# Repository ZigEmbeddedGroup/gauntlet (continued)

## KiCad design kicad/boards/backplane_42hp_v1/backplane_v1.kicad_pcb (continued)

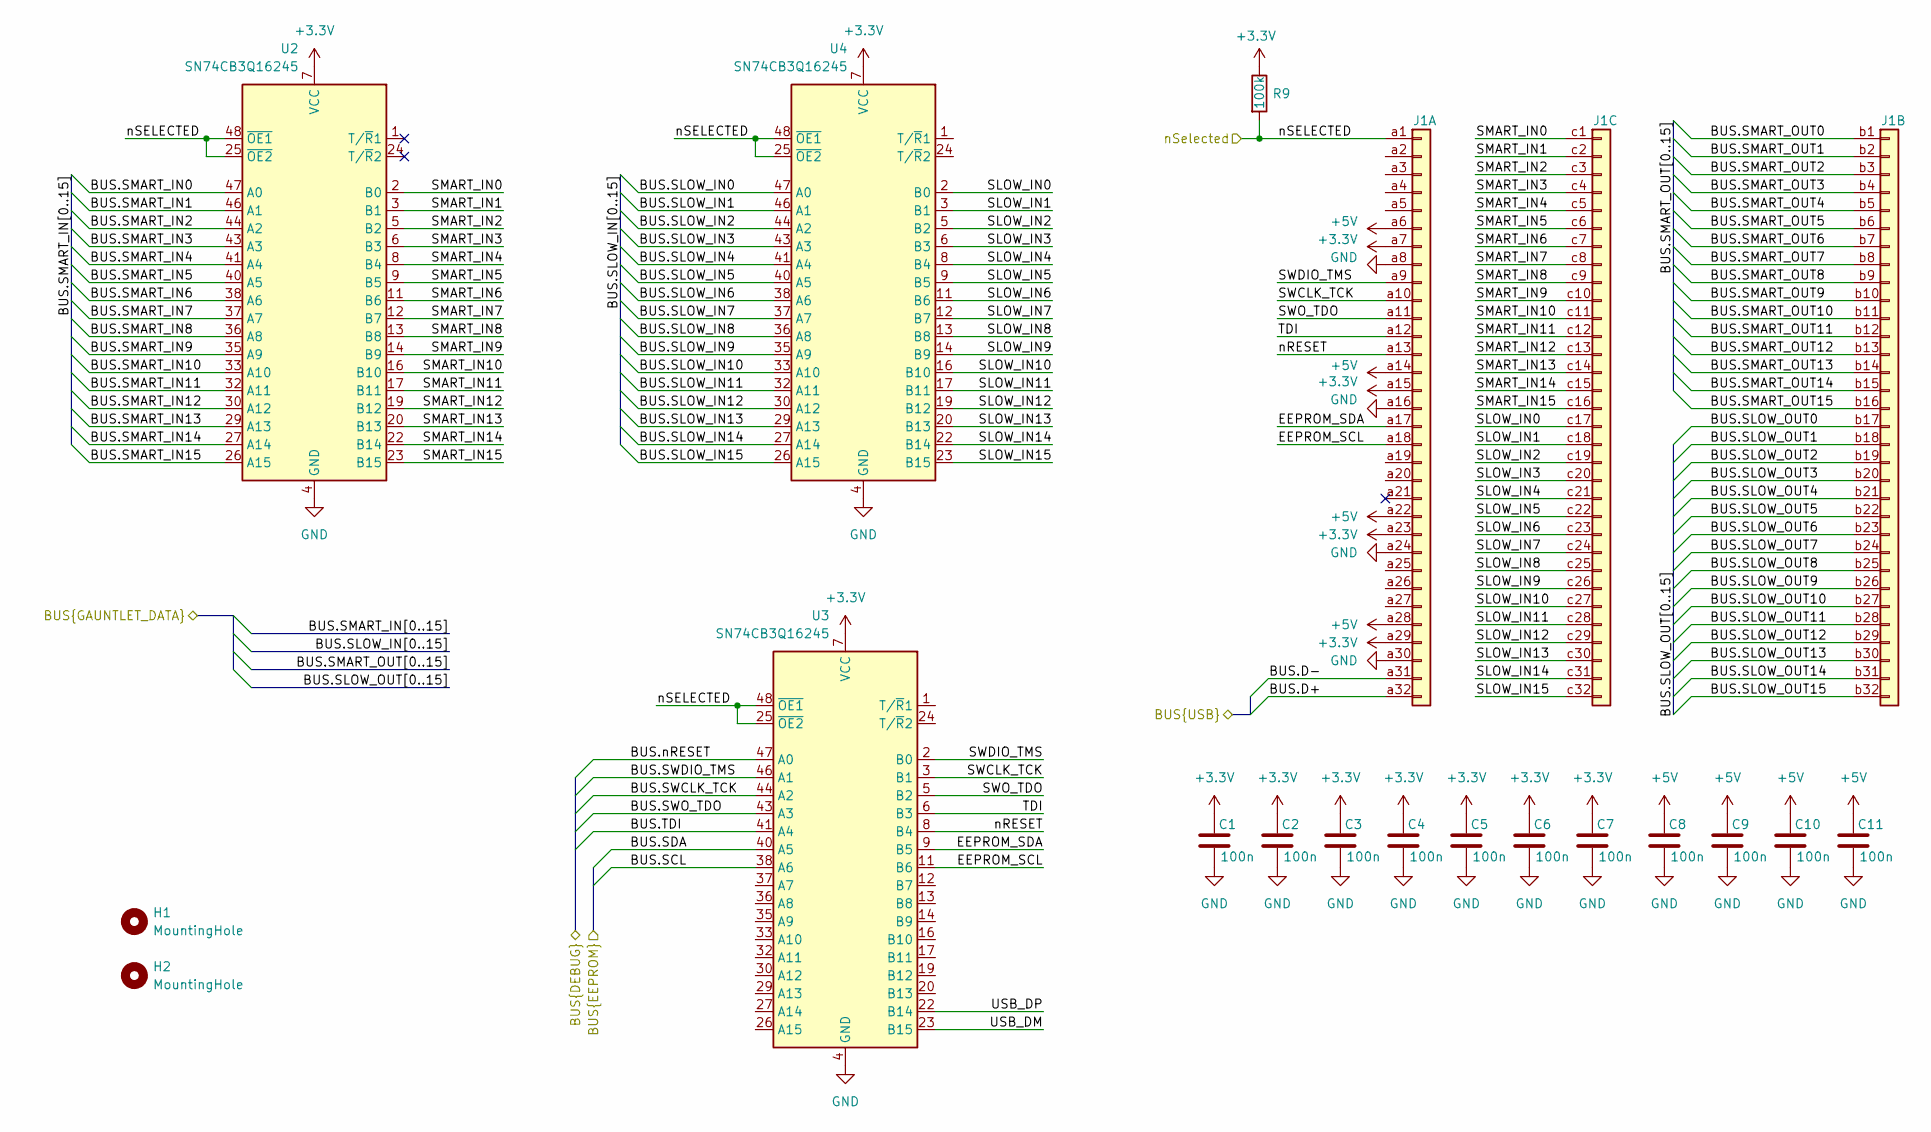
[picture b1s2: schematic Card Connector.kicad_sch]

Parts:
C1, C2, C3, C4, C5, C6, C7, C8, C9, C10, C11: 100n; C_0603_1608Metric
H1, H2: MountingHole; MountingHole_3.2mm_M3
J1: DIN41612_03x32_C_Split; DIN41612_C_3x32_Female_Vertical_THT
R9: 100k; R_0603_1608Metric
U2, U3, U4: SN74CB3Q16245; TSSOP-48_6.1x12.5mm_P0.5mm

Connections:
+3.3V: C1.1, C2.1, C3.1, C4.1, C5.1, C6.1, C7.1, J1.a7, J1.a15, J1.a23, J1.a29, R9.1, U2.7 (VCC), U2.18 (VCC), U2.31 (VCC), U2.42 (VCC), U3.7 (VCC), U3.18 (VCC), U3.31 (VCC), U3.42 (VCC), U4.7 (VCC), U4.18 (VCC), U4.31 (VCC), U4.42 (VCC); also elsewhere on the board
+5V: C8.1, C9.1, C10.1, C11.1, J1.a6, J1.a14, J1.a22, J1.a28; also elsewhere on the board
/BUS.SCL: U3.38 (A6); also elsewhere on the board
/BUS.SDA: U3.40 (A5); also elsewhere on the board
/BUS.SLOW_IN0: U4.47 (A0); also elsewhere on the board
/BUS.SLOW_IN1: U4.46 (A1); also elsewhere on the board
/BUS.SLOW_IN2: U4.44 (A2); also elsewhere on the board
/BUS.SLOW_IN3: U4.43 (A3); also elsewhere on the board
/BUS.SLOW_IN4: U4.41 (A4); also elsewhere on the board
/BUS.SLOW_IN5: U4.40 (A5); also elsewhere on the board
/BUS.SLOW_IN6: U4.38 (A6); also elsewhere on the board
/BUS.SLOW_IN7: U4.37 (A7); also elsewhere on the board
/BUS.SLOW_IN8: U4.36 (A8); also elsewhere on the board
/BUS.SLOW_IN9: U4.35 (A9); also elsewhere on the board
/BUS.SLOW_IN10: U4.33 (A10); also elsewhere on the board
/BUS.SLOW_IN11: U4.32 (A11); also elsewhere on the board
/BUS.SLOW_IN12: U4.30 (A12); also elsewhere on the board
/BUS.SLOW_IN13: U4.29 (A13); also elsewhere on the board
/BUS.SLOW_IN14: U4.27 (A14); also elsewhere on the board
/BUS.SLOW_IN15: U4.26 (A15); also elsewhere on the board
/BUS.SLOW_OUT0: J1.b17; also elsewhere on the board
/BUS.SLOW_OUT1: J1.b18; also elsewhere on the board
/BUS.SLOW_OUT2: J1.b19; also elsewhere on the board
/BUS.SLOW_OUT3: J1.b20; also elsewhere on the board
/BUS.SLOW_OUT4: J1.b21; also elsewhere on the board
/BUS.SLOW_OUT5: J1.b22; also elsewhere on the board
/BUS.SLOW_OUT6: J1.b23; also elsewhere on the board
/BUS.SLOW_OUT7: J1.b24; also elsewhere on the board
/BUS.SLOW_OUT8: J1.b25; also elsewhere on the board
/BUS.SLOW_OUT9: J1.b26; also elsewhere on the board
/BUS.SLOW_OUT10: J1.b27; also elsewhere on the board
/BUS.SLOW_OUT11: J1.b28; also elsewhere on the board
/BUS.SLOW_OUT12: J1.b29; also elsewhere on the board
/BUS.SLOW_OUT13: J1.b30; also elsewhere on the board
/BUS.SLOW_OUT14: J1.b31; also elsewhere on the board
/BUS.SLOW_OUT15: J1.b32; also elsewhere on the board
/BUS.SMART_IN0: U2.47 (A0); also elsewhere on the board
/BUS.SMART_IN1: U2.46 (A1); also elsewhere on the board
/BUS.SMART_IN2: U2.44 (A2); also elsewhere on the board
/BUS.SMART_IN3: U2.43 (A3); also elsewhere on the board
/BUS.SMART_IN4: U2.41 (A4); also elsewhere on the board
/BUS.SMART_IN5: U2.40 (A5); also elsewhere on the board
/BUS.SMART_IN6: U2.38 (A6); also elsewhere on the board
/BUS.SMART_IN7: U2.37 (A7); also elsewhere on the board
/BUS.SMART_IN8: U2.36 (A8); also elsewhere on the board
/BUS.SMART_IN9: U2.35 (A9); also elsewhere on the board
/BUS.SMART_IN10: U2.33 (A10); also elsewhere on the board
/BUS.SMART_IN11: U2.32 (A11); also elsewhere on the board
/BUS.SMART_IN12: U2.30 (A12); also elsewhere on the board
/BUS.SMART_IN13: U2.29 (A13); also elsewhere on the board
/BUS.SMART_IN14: U2.27 (A14); also elsewhere on the board
/BUS.SMART_IN15: U2.26 (A15); also elsewhere on the board
/BUS.SMART_OUT0: J1.b1; also elsewhere on the board
/BUS.SMART_OUT1: J1.b2; also elsewhere on the board
/BUS.SMART_OUT2: J1.b3; also elsewhere on the board
/BUS.SMART_OUT3: J1.b4; also elsewhere on the board
/BUS.SMART_OUT4: J1.b5; also elsewhere on the board
/BUS.SMART_OUT5: J1.b6; also elsewhere on the board
/BUS.SMART_OUT6: J1.b7; also elsewhere on the board
/BUS.SMART_OUT7: J1.b8; also elsewhere on the board
/BUS.SMART_OUT8: J1.b9; also elsewhere on the board
/BUS.SMART_OUT9: J1.b10; also elsewhere on the board
/BUS.SMART_OUT10: J1.b11; also elsewhere on the board
/BUS.SMART_OUT11: J1.b12; also elsewhere on the board
/BUS.SMART_OUT12: J1.b13; also elsewhere on the board
/BUS.SMART_OUT13: J1.b14; also elsewhere on the board
/BUS.SMART_OUT14: J1.b15; also elsewhere on the board
/BUS.SMART_OUT15: J1.b16; also elsewhere on the board
/BUS.SWCLK_TCK: U3.44 (A2); also elsewhere on the board
/BUS.SWDIO_TMS: U3.46 (A1); also elsewhere on the board
/BUS.SWO_TDO: U3.43 (A3); also elsewhere on the board
/BUS.TDI: U3.41 (A4); also elsewhere on the board
/BUS.nRESET: U3.47 (A0); also elsewhere on the board
/Card0/EEPROM_SCL: J1.a18, U3.11 (B6)
/Card0/EEPROM_SDA: J1.a17, U3.9 (B5)
/Card0/SLOW_IN0: J1.c17, U4.2 (B0)
/Card0/SLOW_IN1: J1.c18, U4.3 (B1)
/Card0/SLOW_IN2: J1.c19, U4.5 (B2)
/Card0/SLOW_IN3: J1.c20, U4.6 (B3)
/Card0/SLOW_IN4: J1.c21, U4.8 (B4)
/Card0/SLOW_IN5: J1.c22, U4.9 (B5)
/Card0/SLOW_IN6: J1.c23, U4.11 (B6)
/Card0/SLOW_IN7: J1.c24, U4.12 (B7)
/Card0/SLOW_IN8: J1.c25, U4.13 (B8)
/Card0/SLOW_IN9: J1.c26, U4.14 (B9)
/Card0/SLOW_IN10: J1.c27, U4.16 (B10)
/Card0/SLOW_IN11: J1.c28, U4.17 (B11)
/Card0/SLOW_IN12: J1.c29, U4.19 (B12)
/Card0/SLOW_IN13: J1.c30, U4.20 (B13)
/Card0/SLOW_IN14: J1.c31, U4.22 (B14)
/Card0/SLOW_IN15: J1.c32, U4.23 (B15)
/Card0/SMART_IN0: J1.c1, U2.2 (B0)
/Card0/SMART_IN1: J1.c2, U2.3 (B1)
/Card0/SMART_IN2: J1.c3, U2.5 (B2)
/Card0/SMART_IN3: J1.c4, U2.6 (B3)
/Card0/SMART_IN4: J1.c5, U2.8 (B4)
/Card0/SMART_IN5: J1.c6, U2.9 (B5)
/Card0/SMART_IN6: J1.c7, U2.11 (B6)
/Card0/SMART_IN7: J1.c8, U2.12 (B7)
/Card0/SMART_IN8: J1.c9, U2.13 (B8)
/Card0/SMART_IN9: J1.c10, U2.14 (B9)
/Card0/SMART_IN10: J1.c11, U2.16 (B10)
/Card0/SMART_IN11: J1.c12, U2.17 (B11)
/Card0/SMART_IN12: J1.c13, U2.19 (B12)
/Card0/SMART_IN13: J1.c14, U2.20 (B13)
/Card0/SMART_IN14: J1.c15, U2.22 (B14)
/Card0/SMART_IN15: J1.c16, U2.23 (B15)
/Card0/SWCLK_TCK: J1.a10, U3.3 (B1)
/Card0/SWDIO_TMS: J1.a9, U3.2 (B0)
/Card0/SWO_TDO: J1.a11, U3.5 (B2)
/Card0/TDI: J1.a12, U3.6 (B3)
/Card0/USB_DM: U3.23 (B15)
/Card0/USB_DP: U3.22 (B14)
/Card0/nRESET: J1.a13, U3.8 (B4)
/USB0.D+: J1.a32; also elsewhere on the board
/USB0.D-: J1.a31; also elsewhere on the board
/nCARD0: J1.a1, R9.2, U2.25 (~OE2), U2.48 (~OE1), U3.25 (~OE2), U3.48 (~OE1), U4.25 (~OE2), U4.48 (~OE1); also elsewhere on the board
GND: C1.2, C2.2, C3.2, C4.2, C5.2, C6.2, C7.2, C8.2, C9.2, C10.2, C11.2, J1.a8, J1.a16, J1.a24, J1.a30, U2.4 (GND), U2.10 (GND), U2.15 (GND), U2.21 (GND), U2.28 (GND), U2.34 (GND), U2.39 (GND), U2.45 (GND), U3.4 (GND), U3.10 (GND), U3.15 (GND), U3.21 (GND), U3.28 (GND), U3.34 (GND), U3.39 (GND), U3.45 (GND), U4.4 (GND), U4.10 (GND), U4.15 (GND), U4.21 (GND), U4.28 (GND), U4.34 (GND), U4.39 (GND), U4.45 (GND); also elsewhere on the board

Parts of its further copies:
C16, C17, C18, C19, C20, C21, C22, C23, C24, C25, C26, C27, C28, C29, C30, C31, C32, C33, C34, C35, C36, C37, C38, C39, C40, C41, C42, C43, C44, C45, C46, C47, C48, C49, C50, C51, C52, C53, C54, C55, C56, C57, C58, C59, C60, C61, C62, C63, C64, C65, C66, C67, C68, C69, C70, C71, C72, C73, C74, C75, C76, C77, C78, C79, C80, C81, C82, C83, C84, C85, C86, C87, C88, C89, C90, C91, C92: 100n; C_0603_1608Metric
H3, H4, H5, H6, H7, H8, H9, H10, H11, H12, H13, H14, H15, H16: MountingHole; MountingHole_3.2mm_M3
J3, J4, J5, J6, J7, J8, J9: DIN41612_03x32_C_Split; DIN41612_C_3x32_Female_Vertical_THT
R10, R11, R12, R13, R14, R15, R16: 100k; R_0603_1608Metric
U5, U6, U7, U11, U12, U13, U14, U15, U16, U17, U18, U19, U20, U21, U22, U23, U24, U25, U26, U27, U28: SN74CB3Q16245; TSSOP-48_6.1x12.5mm_P0.5mm

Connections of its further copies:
+3.3V: C16.1, C17.1, C18.1, C19.1, C20.1, C21.1, C22.1, C27.1, C28.1, C29.1, C30.1, C31.1, C32.1, C33.1, C38.1, C39.1, C40.1, C41.1, C42.1, C43.1, C44.1, C49.1, C50.1, C51.1, C52.1, C53.1, C54.1, C55.1, C60.1, C61.1, C62.1, C63.1, C64.1, C65.1, C66.1, C71.1, C72.1, C73.1, C74.1, C75.1, C76.1, C77.1, C82.1, C83.1, C84.1, C85.1, C86.1, C87.1, C88.1, J3.a7, J3.a15, J3.a23, J3.a29, J4.a7, J4.a15, J4.a23, J4.a29, J5.a7, J5.a15, J5.a23, J5.a29, J6.a7, J6.a15, J6.a23, J6.a29, J7.a7, J7.a15, J7.a23, J7.a29, J8.a7, J8.a15, J8.a23, J8.a29, J9.a7, J9.a15, J9.a23, J9.a29, R10.1, R11.1, R12.1, R13.1, R14.1, R15.1, R16.1, U5.7 (VCC), U5.18 (VCC), U5.31 (VCC), U5.42 (VCC), U6.7 (VCC), U6.18 (VCC), U6.31 (VCC), U6.42 (VCC), U7.7 (VCC), U7.18 (VCC), U7.31 (VCC), U7.42 (VCC), U11.7 (VCC), U11.18 (VCC), U11.31 (VCC), U11.42 (VCC), U12.7 (VCC), U12.18 (VCC), U12.31 (VCC), U12.42 (VCC), U13.7 (VCC), U13.18 (VCC), U13.31 (VCC), U13.42 (VCC), U14.7 (VCC), U14.18 (VCC), U14.31 (VCC), U14.42 (VCC), U15.7 (VCC), U15.18 (VCC), U15.31 (VCC), U15.42 (VCC), U16.7 (VCC), U16.18 (VCC), U16.31 (VCC), U16.42 (VCC), U17.7 (VCC), U17.18 (VCC), U17.31 (VCC), U17.42 (VCC), U18.7 (VCC), U18.18 (VCC), U18.31 (VCC), U18.42 (VCC), U19.7 (VCC), U19.18 (VCC), U19.31 (VCC), U19.42 (VCC), U20.7 (VCC), U20.18 (VCC), U20.31 (VCC), U20.42 (VCC), U21.7 (VCC), U21.18 (VCC), U21.31 (VCC), U21.42 (VCC), U22.7 (VCC), U22.18 (VCC), U22.31 (VCC), U22.42 (VCC), U23.7 (VCC), U23.18 (VCC), U23.31 (VCC), U23.42 (VCC), U24.7 (VCC), U24.18 (VCC), U24.31 (VCC), U24.42 (VCC), U25.7 (VCC), U25.18 (VCC), U25.31 (VCC), U25.42 (VCC), U26.7 (VCC), U26.18 (VCC), U26.31 (VCC), U26.42 (VCC), U27.7 (VCC), U27.18 (VCC), U27.31 (VCC), U27.42 (VCC), U28.7 (VCC), U28.18 (VCC), U28.31 (VCC), U28.42 (VCC); also elsewhere on the board
+5V: C23.1, C24.1, C25.1, C26.1, C34.1, C35.1, C36.1, C37.1, C45.1, C46.1, C47.1, C48.1, C56.1, C57.1, C58.1, C59.1, C67.1, C68.1, C69.1, C70.1, C78.1, C79.1, C80.1, C81.1, C89.1, C90.1, C91.1, C92.1, J3.a6, J3.a14, J3.a22, J3.a28, J4.a6, J4.a14, J4.a22, J4.a28, J5.a6, J5.a14, J5.a22, J5.a28, J6.a6, J6.a14, J6.a22, J6.a28, J7.a6, J7.a14, J7.a22, J7.a28, J8.a6, J8.a14, J8.a22, J8.a28, J9.a6, J9.a14, J9.a22, J9.a28; also elsewhere on the board
/BUS.SCL: U6.38 (A6), U12.38 (A6), U15.38 (A6), U18.38 (A6), U21.38 (A6), U24.38 (A6), U27.38 (A6); also elsewhere on the board
/BUS.SDA: U6.40 (A5), U12.40 (A5), U15.40 (A5), U18.40 (A5), U21.40 (A5), U24.40 (A5), U27.40 (A5); also elsewhere on the board
/BUS.SLOW_IN0: U7.47 (A0), U13.47 (A0), U16.47 (A0), U19.47 (A0), U22.47 (A0), U25.47 (A0), U28.47 (A0); also elsewhere on the board
/BUS.SLOW_IN1: U7.46 (A1), U13.46 (A1), U16.46 (A1), U19.46 (A1), U22.46 (A1), U25.46 (A1), U28.46 (A1); also elsewhere on the board
/BUS.SLOW_IN2: U7.44 (A2), U13.44 (A2), U16.44 (A2), U19.44 (A2), U22.44 (A2), U25.44 (A2), U28.44 (A2); also elsewhere on the board
/BUS.SLOW_IN3: U7.43 (A3), U13.43 (A3), U16.43 (A3), U19.43 (A3), U22.43 (A3), U25.43 (A3), U28.43 (A3); also elsewhere on the board
/BUS.SLOW_IN4: U7.41 (A4), U13.41 (A4), U16.41 (A4), U19.41 (A4), U22.41 (A4), U25.41 (A4), U28.41 (A4); also elsewhere on the board
/BUS.SLOW_IN5: U7.40 (A5), U13.40 (A5), U16.40 (A5), U19.40 (A5), U22.40 (A5), U25.40 (A5), U28.40 (A5); also elsewhere on the board
/BUS.SLOW_IN6: U7.38 (A6), U13.38 (A6), U16.38 (A6), U19.38 (A6), U22.38 (A6), U25.38 (A6), U28.38 (A6); also elsewhere on the board
/BUS.SLOW_IN7: U7.37 (A7), U13.37 (A7), U16.37 (A7), U19.37 (A7), U22.37 (A7), U25.37 (A7), U28.37 (A7); also elsewhere on the board
/BUS.SLOW_IN8: U7.36 (A8), U13.36 (A8), U16.36 (A8), U19.36 (A8), U22.36 (A8), U25.36 (A8), U28.36 (A8); also elsewhere on the board
/BUS.SLOW_IN9: U7.35 (A9), U13.35 (A9), U16.35 (A9), U19.35 (A9), U22.35 (A9), U25.35 (A9), U28.35 (A9); also elsewhere on the board
/BUS.SLOW_IN10: U7.33 (A10), U13.33 (A10), U16.33 (A10), U19.33 (A10), U22.33 (A10), U25.33 (A10), U28.33 (A10); also elsewhere on the board
/BUS.SLOW_IN11: U7.32 (A11), U13.32 (A11), U16.32 (A11), U19.32 (A11), U22.32 (A11), U25.32 (A11), U28.32 (A11); also elsewhere on the board
/BUS.SLOW_IN12: U7.30 (A12), U13.30 (A12), U16.30 (A12), U19.30 (A12), U22.30 (A12), U25.30 (A12), U28.30 (A12); also elsewhere on the board
/BUS.SLOW_IN13: U7.29 (A13), U13.29 (A13), U16.29 (A13), U19.29 (A13), U22.29 (A13), U25.29 (A13), U28.29 (A13); also elsewhere on the board
/BUS.SLOW_IN14: U7.27 (A14), U13.27 (A14), U16.27 (A14), U19.27 (A14), U22.27 (A14), U25.27 (A14), U28.27 (A14); also elsewhere on the board
/BUS.SLOW_IN15: U7.26 (A15), U13.26 (A15), U16.26 (A15), U19.26 (A15), U22.26 (A15), U25.26 (A15), U28.26 (A15); also elsewhere on the board
/BUS.SLOW_OUT0: J3.b17, J4.b17, J5.b17, J6.b17, J7.b17, J8.b17, J9.b17; also elsewhere on the board
/BUS.SLOW_OUT1: J3.b18, J4.b18, J5.b18, J6.b18, J7.b18, J8.b18, J9.b18; also elsewhere on the board
/BUS.SLOW_OUT2: J3.b19, J4.b19, J5.b19, J6.b19, J7.b19, J8.b19, J9.b19; also elsewhere on the board
/BUS.SLOW_OUT3: J3.b20, J4.b20, J5.b20, J6.b20, J7.b20, J8.b20, J9.b20; also elsewhere on the board
/BUS.SLOW_OUT4: J3.b21, J4.b21, J5.b21, J6.b21, J7.b21, J8.b21, J9.b21; also elsewhere on the board
/BUS.SLOW_OUT5: J3.b22, J4.b22, J5.b22, J6.b22, J7.b22, J8.b22, J9.b22; also elsewhere on the board
/BUS.SLOW_OUT6: J3.b23, J4.b23, J5.b23, J6.b23, J7.b23, J8.b23, J9.b23; also elsewhere on the board
/BUS.SLOW_OUT7: J3.b24, J4.b24, J5.b24, J6.b24, J7.b24, J8.b24, J9.b24; also elsewhere on the board
/BUS.SLOW_OUT8: J3.b25, J4.b25, J5.b25, J6.b25, J7.b25, J8.b25, J9.b25; also elsewhere on the board
/BUS.SLOW_OUT9: J3.b26, J4.b26, J5.b26, J6.b26, J7.b26, J8.b26, J9.b26; also elsewhere on the board
/BUS.SLOW_OUT10: J3.b27, J4.b27, J5.b27, J6.b27, J7.b27, J8.b27, J9.b27; also elsewhere on the board
/BUS.SLOW_OUT11: J3.b28, J4.b28, J5.b28, J6.b28, J7.b28, J8.b28, J9.b28; also elsewhere on the board
/BUS.SLOW_OUT12: J3.b29, J4.b29, J5.b29, J6.b29, J7.b29, J8.b29, J9.b29; also elsewhere on the board
/BUS.SLOW_OUT13: J3.b30, J4.b30, J5.b30, J6.b30, J7.b30, J8.b30, J9.b30; also elsewhere on the board
/BUS.SLOW_OUT14: J3.b31, J4.b31, J5.b31, J6.b31, J7.b31, J8.b31, J9.b31; also elsewhere on the board
/BUS.SLOW_OUT15: J3.b32, J4.b32, J5.b32, J6.b32, J7.b32, J8.b32, J9.b32; also elsewhere on the board
/BUS.SMART_IN0: U5.47 (A0), U11.47 (A0), U14.47 (A0), U17.47 (A0), U20.47 (A0), U23.47 (A0), U26.47 (A0); also elsewhere on the board
/BUS.SMART_IN1: U5.46 (A1), U11.46 (A1), U14.46 (A1), U17.46 (A1), U20.46 (A1), U23.46 (A1), U26.46 (A1); also elsewhere on the board
/BUS.SMART_IN2: U5.44 (A2), U11.44 (A2), U14.44 (A2), U17.44 (A2), U20.44 (A2), U23.44 (A2), U26.44 (A2); also elsewhere on the board
/BUS.SMART_IN3: U5.43 (A3), U11.43 (A3), U14.43 (A3), U17.43 (A3), U20.43 (A3), U23.43 (A3), U26.43 (A3); also elsewhere on the board
/BUS.SMART_IN4: U5.41 (A4), U11.41 (A4), U14.41 (A4), U17.41 (A4), U20.41 (A4), U23.41 (A4), U26.41 (A4); also elsewhere on the board
/BUS.SMART_IN5: U5.40 (A5), U11.40 (A5), U14.40 (A5), U17.40 (A5), U20.40 (A5), U23.40 (A5), U26.40 (A5); also elsewhere on the board
/BUS.SMART_IN6: U5.38 (A6), U11.38 (A6), U14.38 (A6), U17.38 (A6), U20.38 (A6), U23.38 (A6), U26.38 (A6); also elsewhere on the board
/BUS.SMART_IN7: U5.37 (A7), U11.37 (A7), U14.37 (A7), U17.37 (A7), U20.37 (A7), U23.37 (A7), U26.37 (A7); also elsewhere on the board
/BUS.SMART_IN8: U5.36 (A8), U11.36 (A8), U14.36 (A8), U17.36 (A8), U20.36 (A8), U23.36 (A8), U26.36 (A8); also elsewhere on the board
/BUS.SMART_IN9: U5.35 (A9), U11.35 (A9), U14.35 (A9), U17.35 (A9), U20.35 (A9), U23.35 (A9), U26.35 (A9); also elsewhere on the board
/BUS.SMART_IN10: U5.33 (A10), U11.33 (A10), U14.33 (A10), U17.33 (A10), U20.33 (A10), U23.33 (A10), U26.33 (A10); also elsewhere on the board
/BUS.SMART_IN11: U5.32 (A11), U11.32 (A11), U14.32 (A11), U17.32 (A11), U20.32 (A11), U23.32 (A11), U26.32 (A11); also elsewhere on the board
/BUS.SMART_IN12: U5.30 (A12), U11.30 (A12), U14.30 (A12), U17.30 (A12), U20.30 (A12), U23.30 (A12), U26.30 (A12); also elsewhere on the board
/BUS.SMART_IN13: U5.29 (A13), U11.29 (A13), U14.29 (A13), U17.29 (A13), U20.29 (A13), U23.29 (A13), U26.29 (A13); also elsewhere on the board
/BUS.SMART_IN14: U5.27 (A14), U11.27 (A14), U14.27 (A14), U17.27 (A14), U20.27 (A14), U23.27 (A14), U26.27 (A14); also elsewhere on the board
/BUS.SMART_IN15: U5.26 (A15), U11.26 (A15), U14.26 (A15), U17.26 (A15), U20.26 (A15), U23.26 (A15), U26.26 (A15); also elsewhere on the board
/BUS.SMART_OUT0: J3.b1, J4.b1, J5.b1, J6.b1, J7.b1, J8.b1, J9.b1; also elsewhere on the board
/BUS.SMART_OUT1: J3.b2, J4.b2, J5.b2, J6.b2, J7.b2, J8.b2, J9.b2; also elsewhere on the board
/BUS.SMART_OUT2: J3.b3, J4.b3, J5.b3, J6.b3, J7.b3, J8.b3, J9.b3; also elsewhere on the board
/BUS.SMART_OUT3: J3.b4, J4.b4, J5.b4, J6.b4, J7.b4, J8.b4, J9.b4; also elsewhere on the board
/BUS.SMART_OUT4: J3.b5, J4.b5, J5.b5, J6.b5, J7.b5, J8.b5, J9.b5; also elsewhere on the board
/BUS.SMART_OUT5: J3.b6, J4.b6, J5.b6, J6.b6, J7.b6, J8.b6, J9.b6; also elsewhere on the board
/BUS.SMART_OUT6: J3.b7, J4.b7, J5.b7, J6.b7, J7.b7, J8.b7, J9.b7; also elsewhere on the board
/BUS.SMART_OUT7: J3.b8, J4.b8, J5.b8, J6.b8, J7.b8, J8.b8, J9.b8; also elsewhere on the board
/BUS.SMART_OUT8: J3.b9, J4.b9, J5.b9, J6.b9, J7.b9, J8.b9, J9.b9; also elsewhere on the board
/BUS.SMART_OUT9: J3.b10, J4.b10, J5.b10, J6.b10, J7.b10, J8.b10, J9.b10; also elsewhere on the board
/BUS.SMART_OUT10: J3.b11, J4.b11, J5.b11, J6.b11, J7.b11, J8.b11, J9.b11; also elsewhere on the board
/BUS.SMART_OUT11: J3.b12, J4.b12, J5.b12, J6.b12, J7.b12, J8.b12, J9.b12; also elsewhere on the board
/BUS.SMART_OUT12: J3.b13, J4.b13, J5.b13, J6.b13, J7.b13, J8.b13, J9.b13; also elsewhere on the board
/BUS.SMART_OUT13: J3.b14, J4.b14, J5.b14, J6.b14, J7.b14, J8.b14, J9.b14; also elsewhere on the board
/BUS.SMART_OUT14: J3.b15, J4.b15, J5.b15, J6.b15, J7.b15, J8.b15, J9.b15; also elsewhere on the board
/BUS.SMART_OUT15: J3.b16, J4.b16, J5.b16, J6.b16, J7.b16, J8.b16, J9.b16; also elsewhere on the board
/BUS.SWCLK_TCK: U6.44 (A2), U12.44 (A2), U15.44 (A2), U18.44 (A2), U21.44 (A2), U24.44 (A2), U27.44 (A2); also elsewhere on the board
/BUS.SWDIO_TMS: U6.46 (A1), U12.46 (A1), U15.46 (A1), U18.46 (A1), U21.46 (A1), U24.46 (A1), U27.46 (A1); also elsewhere on the board
/BUS.SWO_TDO: U6.43 (A3), U12.43 (A3), U15.43 (A3), U18.43 (A3), U21.43 (A3), U24.43 (A3), U27.43 (A3); also elsewhere on the board
/BUS.TDI: U6.41 (A4), U12.41 (A4), U15.41 (A4), U18.41 (A4), U21.41 (A4), U24.41 (A4), U27.41 (A4); also elsewhere on the board
/BUS.nRESET: U6.47 (A0), U12.47 (A0), U15.47 (A0), U18.47 (A0), U21.47 (A0), U24.47 (A0), U27.47 (A0); also elsewhere on the board
/Card1/EEPROM_SCL: J3.a18, U6.11 (B6)
/Card1/EEPROM_SDA: J3.a17, U6.9 (B5)
/Card1/SLOW_IN0: J3.c17, U7.2 (B0)
/Card1/SLOW_IN1: J3.c18, U7.3 (B1)
/Card1/SLOW_IN2: J3.c19, U7.5 (B2)
/Card1/SLOW_IN3: J3.c20, U7.6 (B3)
/Card1/SLOW_IN4: J3.c21, U7.8 (B4)
/Card1/SLOW_IN5: J3.c22, U7.9 (B5)
/Card1/SLOW_IN6: J3.c23, U7.11 (B6)
/Card1/SLOW_IN7: J3.c24, U7.12 (B7)
/Card1/SLOW_IN8: J3.c25, U7.13 (B8)
/Card1/SLOW_IN9: J3.c26, U7.14 (B9)
/Card1/SLOW_IN10: J3.c27, U7.16 (B10)
/Card1/SLOW_IN11: J3.c28, U7.17 (B11)
/Card1/SLOW_IN12: J3.c29, U7.19 (B12)
/Card1/SLOW_IN13: J3.c30, U7.20 (B13)
/Card1/SLOW_IN14: J3.c31, U7.22 (B14)
/Card1/SLOW_IN15: J3.c32, U7.23 (B15)
/Card1/SMART_IN0: J3.c1, U5.2 (B0)
/Card1/SMART_IN1: J3.c2, U5.3 (B1)
/Card1/SMART_IN2: J3.c3, U5.5 (B2)
/Card1/SMART_IN3: J3.c4, U5.6 (B3)
/Card1/SMART_IN4: J3.c5, U5.8 (B4)
/Card1/SMART_IN5: J3.c6, U5.9 (B5)
/Card1/SMART_IN6: J3.c7, U5.11 (B6)
/Card1/SMART_IN7: J3.c8, U5.12 (B7)
/Card1/SMART_IN8: J3.c9, U5.13 (B8)
/Card1/SMART_IN9: J3.c10, U5.14 (B9)
/Card1/SMART_IN10: J3.c11, U5.16 (B10)
/Card1/SMART_IN11: J3.c12, U5.17 (B11)
/Card1/SMART_IN12: J3.c13, U5.19 (B12)
/Card1/SMART_IN13: J3.c14, U5.20 (B13)
/Card1/SMART_IN14: J3.c15, U5.22 (B14)
/Card1/SMART_IN15: J3.c16, U5.23 (B15)
/Card1/SWCLK_TCK: J3.a10, U6.3 (B1)
/Card1/SWDIO_TMS: J3.a9, U6.2 (B0)
/Card1/SWO_TDO: J3.a11, U6.5 (B2)
/Card1/TDI: J3.a12, U6.6 (B3)
/Card1/USB_DM: U6.23 (B15)
/Card1/USB_DP: U6.22 (B14)
/Card1/nRESET: J3.a13, U6.8 (B4)
/Card2/EEPROM_SCL: J4.a18, U12.11 (B6)
/Card2/EEPROM_SDA: J4.a17, U12.9 (B5)
/Card2/SLOW_IN0: J4.c17, U13.2 (B0)
/Card2/SLOW_IN1: J4.c18, U13.3 (B1)
/Card2/SLOW_IN2: J4.c19, U13.5 (B2)
/Card2/SLOW_IN3: J4.c20, U13.6 (B3)
/Card2/SLOW_IN4: J4.c21, U13.8 (B4)
/Card2/SLOW_IN5: J4.c22, U13.9 (B5)
/Card2/SLOW_IN6: J4.c23, U13.11 (B6)
/Card2/SLOW_IN7: J4.c24, U13.12 (B7)
/Card2/SLOW_IN8: J4.c25, U13.13 (B8)
/Card2/SLOW_IN9: J4.c26, U13.14 (B9)
/Card2/SLOW_IN10: J4.c27, U13.16 (B10)
/Card2/SLOW_IN11: J4.c28, U13.17 (B11)
/Card2/SLOW_IN12: J4.c29, U13.19 (B12)
/Card2/SLOW_IN13: J4.c30, U13.20 (B13)
/Card2/SLOW_IN14: J4.c31, U13.22 (B14)
/Card2/SLOW_IN15: J4.c32, U13.23 (B15)
/Card2/SMART_IN0: J4.c1, U11.2 (B0)
/Card2/SMART_IN1: J4.c2, U11.3 (B1)
/Card2/SMART_IN2: J4.c3, U11.5 (B2)
/Card2/SMART_IN3: J4.c4, U11.6 (B3)
/Card2/SMART_IN4: J4.c5, U11.8 (B4)
/Card2/SMART_IN5: J4.c6, U11.9 (B5)
/Card2/SMART_IN6: J4.c7, U11.11 (B6)
/Card2/SMART_IN7: J4.c8, U11.12 (B7)
/Card2/SMART_IN8: J4.c9, U11.13 (B8)
/Card2/SMART_IN9: J4.c10, U11.14 (B9)
/Card2/SMART_IN10: J4.c11, U11.16 (B10)
/Card2/SMART_IN11: J4.c12, U11.17 (B11)
/Card2/SMART_IN12: J4.c13, U11.19 (B12)
/Card2/SMART_IN13: J4.c14, U11.20 (B13)
/Card2/SMART_IN14: J4.c15, U11.22 (B14)
/Card2/SMART_IN15: J4.c16, U11.23 (B15)
/Card2/SWCLK_TCK: J4.a10, U12.3 (B1)
/Card2/SWDIO_TMS: J4.a9, U12.2 (B0)
/Card2/SWO_TDO: J4.a11, U12.5 (B2)
/Card2/TDI: J4.a12, U12.6 (B3)
/Card2/USB_DM: U12.23 (B15)
/Card2/USB_DP: U12.22 (B14)
/Card2/nRESET: J4.a13, U12.8 (B4)
/Card3/EEPROM_SCL: J5.a18, U15.11 (B6)
/Card3/EEPROM_SDA: J5.a17, U15.9 (B5)
/Card3/SLOW_IN0: J5.c17, U16.2 (B0)
/Card3/SLOW_IN1: J5.c18, U16.3 (B1)
/Card3/SLOW_IN2: J5.c19, U16.5 (B2)
/Card3/SLOW_IN3: J5.c20, U16.6 (B3)
/Card3/SLOW_IN4: J5.c21, U16.8 (B4)
/Card3/SLOW_IN5: J5.c22, U16.9 (B5)
/Card3/SLOW_IN6: J5.c23, U16.11 (B6)
/Card3/SLOW_IN7: J5.c24, U16.12 (B7)
/Card3/SLOW_IN8: J5.c25, U16.13 (B8)
/Card3/SLOW_IN9: J5.c26, U16.14 (B9)
/Card3/SLOW_IN10: J5.c27, U16.16 (B10)
/Card3/SLOW_IN11: J5.c28, U16.17 (B11)
/Card3/SLOW_IN12: J5.c29, U16.19 (B12)
/Card3/SLOW_IN13: J5.c30, U16.20 (B13)
/Card3/SLOW_IN14: J5.c31, U16.22 (B14)
/Card3/SLOW_IN15: J5.c32, U16.23 (B15)
/Card3/SMART_IN0: J5.c1, U14.2 (B0)
/Card3/SMART_IN1: J5.c2, U14.3 (B1)
/Card3/SMART_IN2: J5.c3, U14.5 (B2)
/Card3/SMART_IN3: J5.c4, U14.6 (B3)
/Card3/SMART_IN4: J5.c5, U14.8 (B4)
/Card3/SMART_IN5: J5.c6, U14.9 (B5)
/Card3/SMART_IN6: J5.c7, U14.11 (B6)
/Card3/SMART_IN7: J5.c8, U14.12 (B7)
/Card3/SMART_IN8: J5.c9, U14.13 (B8)
/Card3/SMART_IN9: J5.c10, U14.14 (B9)
/Card3/SMART_IN10: J5.c11, U14.16 (B10)
/Card3/SMART_IN11: J5.c12, U14.17 (B11)
/Card3/SMART_IN12: J5.c13, U14.19 (B12)
/Card3/SMART_IN13: J5.c14, U14.20 (B13)
/Card3/SMART_IN14: J5.c15, U14.22 (B14)
/Card3/SMART_IN15: J5.c16, U14.23 (B15)
/Card3/SWCLK_TCK: J5.a10, U15.3 (B1)
/Card3/SWDIO_TMS: J5.a9, U15.2 (B0)
/Card3/SWO_TDO: J5.a11, U15.5 (B2)
/Card3/TDI: J5.a12, U15.6 (B3)
/Card3/USB_DM: U15.23 (B15)
/Card3/USB_DP: U15.22 (B14)
/Card3/nRESET: J5.a13, U15.8 (B4)
/Card4/EEPROM_SCL: J6.a18, U18.11 (B6)
/Card4/EEPROM_SDA: J6.a17, U18.9 (B5)
/Card4/SLOW_IN0: J6.c17, U19.2 (B0)
/Card4/SLOW_IN1: J6.c18, U19.3 (B1)
/Card4/SLOW_IN2: J6.c19, U19.5 (B2)
/Card4/SLOW_IN3: J6.c20, U19.6 (B3)
/Card4/SLOW_IN4: J6.c21, U19.8 (B4)
/Card4/SLOW_IN5: J6.c22, U19.9 (B5)
/Card4/SLOW_IN6: J6.c23, U19.11 (B6)
/Card4/SLOW_IN7: J6.c24, U19.12 (B7)
/Card4/SLOW_IN8: J6.c25, U19.13 (B8)
/Card4/SLOW_IN9: J6.c26, U19.14 (B9)
/Card4/SLOW_IN10: J6.c27, U19.16 (B10)
/Card4/SLOW_IN11: J6.c28, U19.17 (B11)
/Card4/SLOW_IN12: J6.c29, U19.19 (B12)
/Card4/SLOW_IN13: J6.c30, U19.20 (B13)
/Card4/SLOW_IN14: J6.c31, U19.22 (B14)
/Card4/SLOW_IN15: J6.c32, U19.23 (B15)
/Card4/SMART_IN0: J6.c1, U17.2 (B0)
/Card4/SMART_IN1: J6.c2, U17.3 (B1)
/Card4/SMART_IN2: J6.c3, U17.5 (B2)
/Card4/SMART_IN3: J6.c4, U17.6 (B3)
/Card4/SMART_IN4: J6.c5, U17.8 (B4)
/Card4/SMART_IN5: J6.c6, U17.9 (B5)
/Card4/SMART_IN6: J6.c7, U17.11 (B6)
/Card4/SMART_IN7: J6.c8, U17.12 (B7)
/Card4/SMART_IN8: J6.c9, U17.13 (B8)
/Card4/SMART_IN9: J6.c10, U17.14 (B9)
/Card4/SMART_IN10: J6.c11, U17.16 (B10)
/Card4/SMART_IN11: J6.c12, U17.17 (B11)
/Card4/SMART_IN12: J6.c13, U17.19 (B12)
/Card4/SMART_IN13: J6.c14, U17.20 (B13)
/Card4/SMART_IN14: J6.c15, U17.22 (B14)
/Card4/SMART_IN15: J6.c16, U17.23 (B15)
/Card4/SWCLK_TCK: J6.a10, U18.3 (B1)
/Card4/SWDIO_TMS: J6.a9, U18.2 (B0)
/Card4/SWO_TDO: J6.a11, U18.5 (B2)
/Card4/TDI: J6.a12, U18.6 (B3)
/Card4/USB_DM: U18.23 (B15)
/Card4/USB_DP: U18.22 (B14)
/Card4/nRESET: J6.a13, U18.8 (B4)
/Card5/EEPROM_SCL: J7.a18, U21.11 (B6)
/Card5/EEPROM_SDA: J7.a17, U21.9 (B5)
/Card5/SLOW_IN0: J7.c17, U22.2 (B0)
/Card5/SLOW_IN1: J7.c18, U22.3 (B1)
/Card5/SLOW_IN2: J7.c19, U22.5 (B2)
/Card5/SLOW_IN3: J7.c20, U22.6 (B3)
/Card5/SLOW_IN4: J7.c21, U22.8 (B4)
/Card5/SLOW_IN5: J7.c22, U22.9 (B5)
/Card5/SLOW_IN6: J7.c23, U22.11 (B6)
/Card5/SLOW_IN7: J7.c24, U22.12 (B7)
/Card5/SLOW_IN8: J7.c25, U22.13 (B8)
/Card5/SLOW_IN9: J7.c26, U22.14 (B9)
/Card5/SLOW_IN10: J7.c27, U22.16 (B10)
/Card5/SLOW_IN11: J7.c28, U22.17 (B11)
/Card5/SLOW_IN12: J7.c29, U22.19 (B12)
/Card5/SLOW_IN13: J7.c30, U22.20 (B13)
/Card5/SLOW_IN14: J7.c31, U22.22 (B14)
/Card5/SLOW_IN15: J7.c32, U22.23 (B15)
/Card5/SMART_IN0: J7.c1, U20.2 (B0)
/Card5/SMART_IN1: J7.c2, U20.3 (B1)
/Card5/SMART_IN2: J7.c3, U20.5 (B2)
/Card5/SMART_IN3: J7.c4, U20.6 (B3)
/Card5/SMART_IN4: J7.c5, U20.8 (B4)
/Card5/SMART_IN5: J7.c6, U20.9 (B5)
/Card5/SMART_IN6: J7.c7, U20.11 (B6)
/Card5/SMART_IN7: J7.c8, U20.12 (B7)
/Card5/SMART_IN8: J7.c9, U20.13 (B8)
/Card5/SMART_IN9: J7.c10, U20.14 (B9)
/Card5/SMART_IN10: J7.c11, U20.16 (B10)
/Card5/SMART_IN11: J7.c12, U20.17 (B11)
/Card5/SMART_IN12: J7.c13, U20.19 (B12)
/Card5/SMART_IN13: J7.c14, U20.20 (B13)
/Card5/SMART_IN14: J7.c15, U20.22 (B14)
/Card5/SMART_IN15: J7.c16, U20.23 (B15)
/Card5/SWCLK_TCK: J7.a10, U21.3 (B1)
/Card5/SWDIO_TMS: J7.a9, U21.2 (B0)
/Card5/SWO_TDO: J7.a11, U21.5 (B2)
/Card5/TDI: J7.a12, U21.6 (B3)
/Card5/USB_DM: U21.23 (B15)
/Card5/USB_DP: U21.22 (B14)
/Card5/nRESET: J7.a13, U21.8 (B4)
/Card6/EEPROM_SCL: J8.a18, U24.11 (B6)
/Card6/EEPROM_SDA: J8.a17, U24.9 (B5)
/Card6/SLOW_IN0: J8.c17, U25.2 (B0)
/Card6/SLOW_IN1: J8.c18, U25.3 (B1)
/Card6/SLOW_IN2: J8.c19, U25.5 (B2)
/Card6/SLOW_IN3: J8.c20, U25.6 (B3)
/Card6/SLOW_IN4: J8.c21, U25.8 (B4)
/Card6/SLOW_IN5: J8.c22, U25.9 (B5)
/Card6/SLOW_IN6: J8.c23, U25.11 (B6)
/Card6/SLOW_IN7: J8.c24, U25.12 (B7)
/Card6/SLOW_IN8: J8.c25, U25.13 (B8)
/Card6/SLOW_IN9: J8.c26, U25.14 (B9)
/Card6/SLOW_IN10: J8.c27, U25.16 (B10)
/Card6/SLOW_IN11: J8.c28, U25.17 (B11)
/Card6/SLOW_IN12: J8.c29, U25.19 (B12)
/Card6/SLOW_IN13: J8.c30, U25.20 (B13)
/Card6/SLOW_IN14: J8.c31, U25.22 (B14)
/Card6/SLOW_IN15: J8.c32, U25.23 (B15)
/Card6/SMART_IN0: J8.c1, U23.2 (B0)
/Card6/SMART_IN1: J8.c2, U23.3 (B1)
/Card6/SMART_IN2: J8.c3, U23.5 (B2)
/Card6/SMART_IN3: J8.c4, U23.6 (B3)
/Card6/SMART_IN4: J8.c5, U23.8 (B4)
/Card6/SMART_IN5: J8.c6, U23.9 (B5)
/Card6/SMART_IN6: J8.c7, U23.11 (B6)
/Card6/SMART_IN7: J8.c8, U23.12 (B7)
/Card6/SMART_IN8: J8.c9, U23.13 (B8)
/Card6/SMART_IN9: J8.c10, U23.14 (B9)
/Card6/SMART_IN10: J8.c11, U23.16 (B10)
/Card6/SMART_IN11: J8.c12, U23.17 (B11)
/Card6/SMART_IN12: J8.c13, U23.19 (B12)
/Card6/SMART_IN13: J8.c14, U23.20 (B13)
/Card6/SMART_IN14: J8.c15, U23.22 (B14)
/Card6/SMART_IN15: J8.c16, U23.23 (B15)
/Card6/SWCLK_TCK: J8.a10, U24.3 (B1)
/Card6/SWDIO_TMS: J8.a9, U24.2 (B0)
/Card6/SWO_TDO: J8.a11, U24.5 (B2)
/Card6/TDI: J8.a12, U24.6 (B3)
/Card6/USB_DM: U24.23 (B15)
/Card6/USB_DP: U24.22 (B14)
/Card6/nRESET: J8.a13, U24.8 (B4)
/Card7/EEPROM_SCL: J9.a18, U27.11 (B6)
/Card7/EEPROM_SDA: J9.a17, U27.9 (B5)
/Card7/SLOW_IN0: J9.c17, U28.2 (B0)
/Card7/SLOW_IN1: J9.c18, U28.3 (B1)
/Card7/SLOW_IN2: J9.c19, U28.5 (B2)
/Card7/SLOW_IN3: J9.c20, U28.6 (B3)
/Card7/SLOW_IN4: J9.c21, U28.8 (B4)
/Card7/SLOW_IN5: J9.c22, U28.9 (B5)
/Card7/SLOW_IN6: J9.c23, U28.11 (B6)
/Card7/SLOW_IN7: J9.c24, U28.12 (B7)
/Card7/SLOW_IN8: J9.c25, U28.13 (B8)
/Card7/SLOW_IN9: J9.c26, U28.14 (B9)
/Card7/SLOW_IN10: J9.c27, U28.16 (B10)
/Card7/SLOW_IN11: J9.c28, U28.17 (B11)
/Card7/SLOW_IN12: J9.c29, U28.19 (B12)
/Card7/SLOW_IN13: J9.c30, U28.20 (B13)
/Card7/SLOW_IN14: J9.c31, U28.22 (B14)
/Card7/SLOW_IN15: J9.c32, U28.23 (B15)
/Card7/SMART_IN0: J9.c1, U26.2 (B0)
/Card7/SMART_IN1: J9.c2, U26.3 (B1)
/Card7/SMART_IN2: J9.c3, U26.5 (B2)
/Card7/SMART_IN3: J9.c4, U26.6 (B3)
/Card7/SMART_IN4: J9.c5, U26.8 (B4)
/Card7/SMART_IN5: J9.c6, U26.9 (B5)
/Card7/SMART_IN6: J9.c7, U26.11 (B6)
/Card7/SMART_IN7: J9.c8, U26.12 (B7)
/Card7/SMART_IN8: J9.c9, U26.13 (B8)
/Card7/SMART_IN9: J9.c10, U26.14 (B9)
/Card7/SMART_IN10: J9.c11, U26.16 (B10)
/Card7/SMART_IN11: J9.c12, U26.17 (B11)
/Card7/SMART_IN12: J9.c13, U26.19 (B12)
/Card7/SMART_IN13: J9.c14, U26.20 (B13)
/Card7/SMART_IN14: J9.c15, U26.22 (B14)
/Card7/SMART_IN15: J9.c16, U26.23 (B15)
/Card7/SWCLK_TCK: J9.a10, U27.3 (B1)
/Card7/SWDIO_TMS: J9.a9, U27.2 (B0)
/Card7/SWO_TDO: J9.a11, U27.5 (B2)
/Card7/TDI: J9.a12, U27.6 (B3)
/Card7/USB_DM: U27.23 (B15)
/Card7/USB_DP: U27.22 (B14)
/Card7/nRESET: J9.a13, U27.8 (B4)
/USB1.D+: J3.a32; also elsewhere on the board
/USB1.D-: J3.a31; also elsewhere on the board
/USB2.D+: J4.a32; also elsewhere on the board
/USB2.D-: J4.a31; also elsewhere on the board
/USB3.D+: J5.a32; also elsewhere on the board
/USB3.D-: J5.a31; also elsewhere on the board
/USB4.D+: J6.a32; also elsewhere on the board
/USB4.D-: J6.a31; also elsewhere on the board
/USB5.D+: J7.a32; also elsewhere on the board
/USB5.D-: J7.a31; also elsewhere on the board
/USB6.D+: J8.a32; also elsewhere on the board
/USB6.D-: J8.a31; also elsewhere on the board
/USB7.D+: J9.a32; also elsewhere on the board
/USB7.D-: J9.a31; also elsewhere on the board
/nCARD1: J3.a1, R10.2, U5.25 (~OE2), U5.48 (~OE1), U6.25 (~OE2), U6.48 (~OE1), U7.25 (~OE2), U7.48 (~OE1); also elsewhere on the board
/nCARD2: J4.a1, R11.2, U11.25 (~OE2), U11.48 (~OE1), U12.25 (~OE2), U12.48 (~OE1), U13.25 (~OE2), U13.48 (~OE1); also elsewhere on the board
/nCARD3: J5.a1, R12.2, U14.25 (~OE2), U14.48 (~OE1), U15.25 (~OE2), U15.48 (~OE1), U16.25 (~OE2), U16.48 (~OE1); also elsewhere on the board
/nCARD4: J6.a1, R13.2, U17.25 (~OE2), U17.48 (~OE1), U18.25 (~OE2), U18.48 (~OE1), U19.25 (~OE2), U19.48 (~OE1); also elsewhere on the board
/nCARD5: J7.a1, R14.2, U20.25 (~OE2), U20.48 (~OE1), U21.25 (~OE2), U21.48 (~OE1), U22.25 (~OE2), U22.48 (~OE1); also elsewhere on the board
/nCARD6: J8.a1, R15.2, U23.25 (~OE2), U23.48 (~OE1), U24.25 (~OE2), U24.48 (~OE1), U25.25 (~OE2), U25.48 (~OE1); also elsewhere on the board
/nCARD7: J9.a1, R16.2, U26.25 (~OE2), U26.48 (~OE1), U27.25 (~OE2), U27.48 (~OE1), U28.25 (~OE2), U28.48 (~OE1); also elsewhere on the board
GND: C16.2, C17.2, C18.2, C19.2, C20.2, C21.2, C22.2, C23.2, C24.2, C25.2, C26.2, C27.2, C28.2, C29.2, C30.2, C31.2, C32.2, C33.2, C34.2, C35.2, C36.2, C37.2, C38.2, C39.2, C40.2, C41.2, C42.2, C43.2, C44.2, C45.2, C46.2, C47.2, C48.2, C49.2, C50.2, C51.2, C52.2, C53.2, C54.2, C55.2, C56.2, C57.2, C58.2, C59.2, C60.2, C61.2, C62.2, C63.2, C64.2, C65.2, C66.2, C67.2, C68.2, C69.2, C70.2, C71.2, C72.2, C73.2, C74.2, C75.2, C76.2, C77.2, C78.2, C79.2, C80.2, C81.2, C82.2, C83.2, C84.2, C85.2, C86.2, C87.2, C88.2, C89.2, C90.2, C91.2, C92.2, J3.a8, J3.a16, J3.a24, J3.a30, J4.a8, J4.a16, J4.a24, J4.a30, J5.a8, J5.a16, J5.a24, J5.a30, J6.a8, J6.a16, J6.a24, J6.a30, J7.a8, J7.a16, J7.a24, J7.a30, J8.a8, J8.a16, J8.a24, J8.a30, J9.a8, J9.a16, J9.a24, J9.a30, U5.4 (GND), U5.10 (GND), U5.15 (GND), U5.21 (GND), U5.28 (GND), U5.34 (GND), U5.39 (GND), U5.45 (GND), U6.4 (GND), U6.10 (GND), U6.15 (GND), U6.21 (GND), U6.28 (GND), U6.34 (GND), U6.39 (GND), U6.45 (GND), U7.4 (GND), U7.10 (GND), U7.15 (GND), U7.21 (GND), U7.28 (GND), U7.34 (GND), U7.39 (GND), U7.45 (GND), U11.4 (GND), U11.10 (GND), U11.15 (GND), U11.21 (GND), U11.28 (GND), U11.34 (GND), U11.39 (GND), U11.45 (GND), U12.4 (GND), U12.10 (GND), U12.15 (GND), U12.21 (GND), U12.28 (GND), U12.34 (GND), U12.39 (GND), U12.45 (GND), U13.4 (GND), U13.10 (GND), U13.15 (GND), U13.21 (GND), U13.28 (GND), U13.34 (GND), U13.39 (GND), U13.45 (GND), U14.4 (GND), U14.10 (GND), U14.15 (GND), U14.21 (GND), U14.28 (GND), U14.34 (GND), U14.39 (GND), U14.45 (GND), U15.4 (GND), U15.10 (GND), U15.15 (GND), U15.21 (GND), U15.28 (GND), U15.34 (GND), U15.39 (GND), U15.45 (GND), U16.4 (GND), U16.10 (GND), U16.15 (GND), U16.21 (GND), U16.28 (GND), U16.34 (GND), U16.39 (GND), U16.45 (GND), U17.4 (GND), U17.10 (GND), U17.15 (GND), U17.21 (GND), U17.28 (GND), U17.34 (GND), U17.39 (GND), U17.45 (GND), U18.4 (GND), U18.10 (GND), U18.15 (GND), U18.21 (GND), U18.28 (GND), U18.34 (GND), U18.39 (GND), U18.45 (GND), U19.4 (GND), U19.10 (GND), U19.15 (GND), U19.21 (GND), U19.28 (GND), U19.34 (GND), U19.39 (GND), U19.45 (GND), U20.4 (GND), U20.10 (GND), U20.15 (GND), U20.21 (GND), U20.28 (GND), U20.34 (GND), U20.39 (GND), U20.45 (GND), U21.4 (GND), U21.10 (GND), U21.15 (GND), U21.21 (GND), U21.28 (GND), U21.34 (GND), U21.39 (GND), U21.45 (GND), U22.4 (GND), U22.10 (GND), U22.15 (GND), U22.21 (GND), U22.28 (GND), U22.34 (GND), U22.39 (GND), U22.45 (GND), U23.4 (GND), U23.10 (GND), U23.15 (GND), U23.21 (GND), U23.28 (GND), U23.34 (GND), U23.39 (GND), U23.45 (GND), U24.4 (GND), U24.10 (GND), U24.15 (GND), U24.21 (GND), U24.28 (GND), U24.34 (GND), U24.39 (GND), U24.45 (GND), U25.4 (GND), U25.10 (GND), U25.15 (GND), U25.21 (GND), U25.28 (GND), U25.34 (GND), U25.39 (GND), U25.45 (GND), U26.4 (GND), U26.10 (GND), U26.15 (GND), U26.21 (GND), U26.28 (GND), U26.34 (GND), U26.39 (GND), U26.45 (GND), U27.4 (GND), U27.10 (GND), U27.15 (GND), U27.21 (GND), U27.28 (GND), U27.34 (GND), U27.39 (GND), U27.45 (GND), U28.4 (GND), U28.10 (GND), U28.15 (GND), U28.21 (GND), U28.28 (GND), U28.34 (GND), U28.39 (GND), U28.45 (GND); also elsewhere on the board

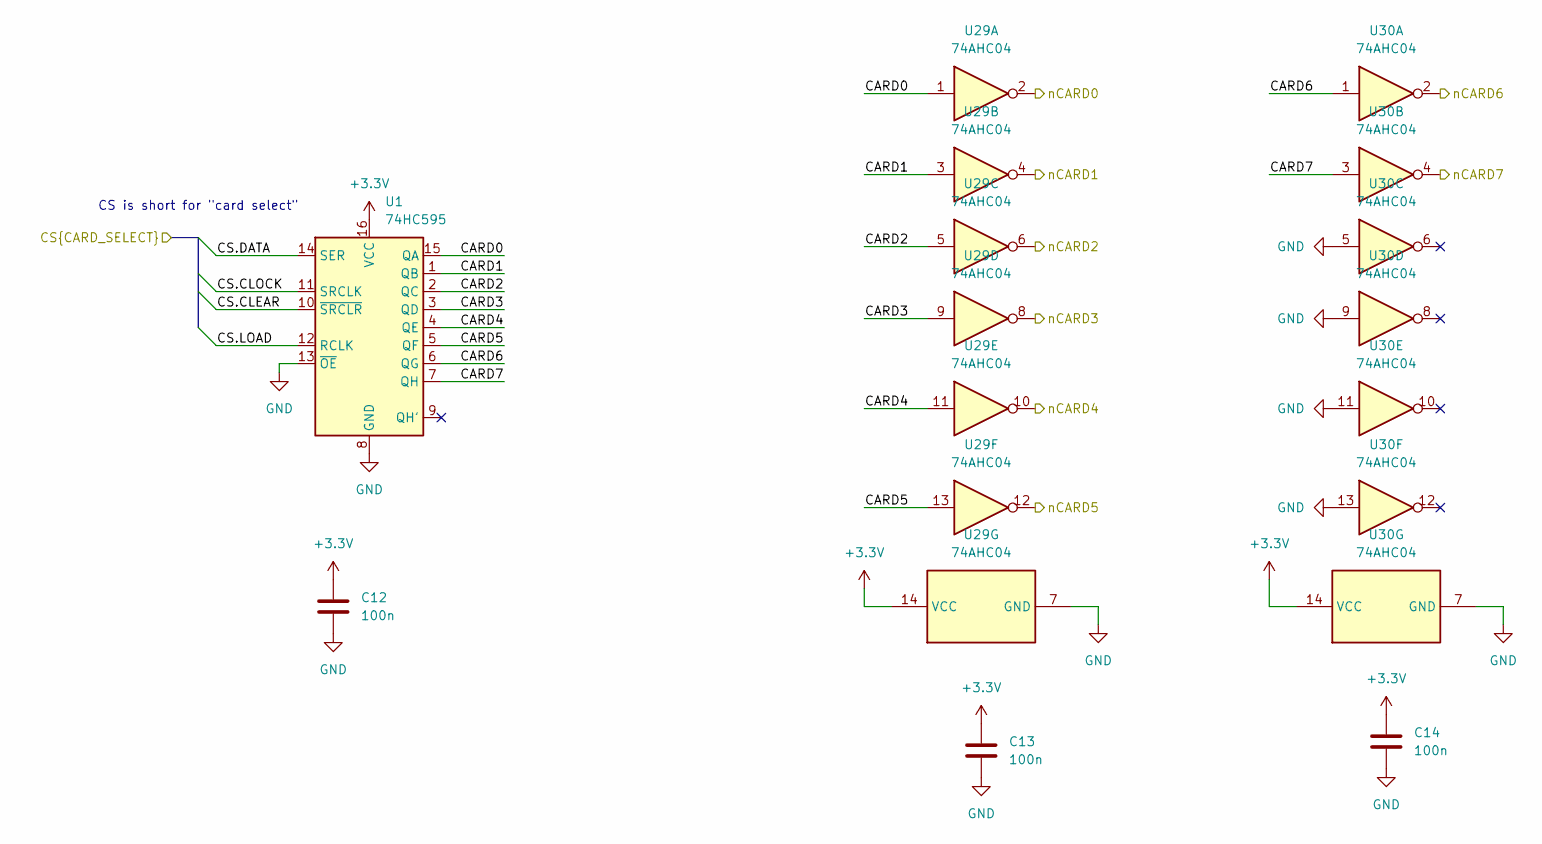
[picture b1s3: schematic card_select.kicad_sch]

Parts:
C12, C13, C14: 100n; C_0805_2012Metric
U1: 74HC595; TSSOP-16_4.4x5mm_P0.65mm; LCSC C5948
U29, U30: 74AHC04; TSSOP-14_4.4x5mm_P0.65mm; LCSC C415550

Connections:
+3.3V: C12.1, C13.1, C14.1, U1.16 (VCC), U29.14 (VCC), U30.14 (VCC); also elsewhere on the board
/CS.CLEAR: U1.10 (~SRCLR); also elsewhere on the board
/CS.CLOCK: U1.11 (SRCLK); also elsewhere on the board
/CS.DATA: U1.14 (SER); also elsewhere on the board
/CS.LOAD: U1.12 (RCLK); also elsewhere on the board
/Card Select/CARD0: U1.15 (QA), U29.1
/Card Select/CARD1: U1.1 (QB), U29.3
/Card Select/CARD2: U1.2 (QC), U29.5
/Card Select/CARD3: U1.3 (QD), U29.9
/Card Select/CARD4: U1.4 (QE), U29.11
/Card Select/CARD5: U1.5 (QF), U29.13
/Card Select/CARD6: U1.6 (QG), U30.1
/Card Select/CARD7: U1.7 (QH), U30.3
/nCARD0: U29.2; also elsewhere on the board
/nCARD1: U29.4; also elsewhere on the board
/nCARD2: U29.6; also elsewhere on the board
/nCARD3: U29.8; also elsewhere on the board
/nCARD4: U29.10; also elsewhere on the board
/nCARD5: U29.12; also elsewhere on the board
/nCARD6: U30.2; also elsewhere on the board
/nCARD7: U30.4; also elsewhere on the board
GND: C12.2, C13.2, C14.2, U1.8 (GND), U1.13 (~OE), U29.7 (GND), U30.5, U30.7 (GND), U30.9, U30.11, U30.13; also elsewhere on the board

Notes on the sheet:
CS is short for "card select"
